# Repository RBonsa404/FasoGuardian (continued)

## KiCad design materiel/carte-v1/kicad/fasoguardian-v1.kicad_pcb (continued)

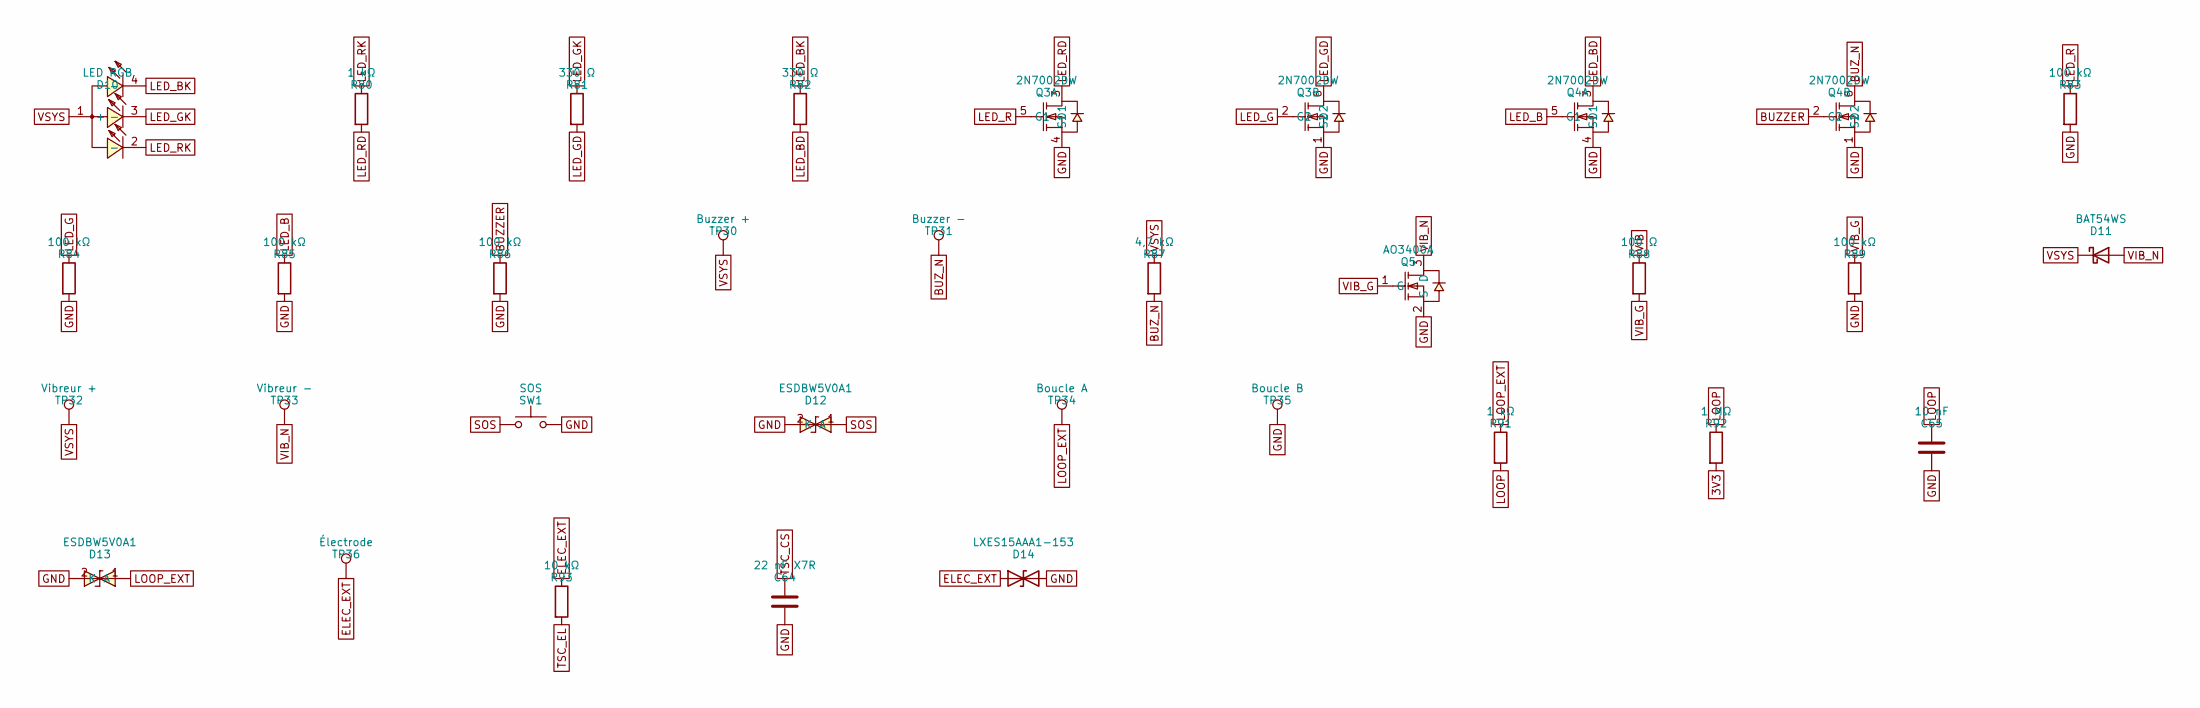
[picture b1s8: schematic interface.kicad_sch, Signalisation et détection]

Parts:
C64: 22 nF X7R; C_0402_1005Metric; LCSC C1532
C65: 10 nF; C_0402_1005Metric; LCSC C15195
D10: LED RGB; LED-ARRAY-SMD_4P-L1.0-W1.0-TR-RD; LCSC C158099
D11: BAT54WS; D_SOD-323; LCSC C22629
D12, D13: ESDBW5V0A1; X1-DFN1006-2_L1.0-W0.6-P0.65-BI; LCSC C5173252
D14: LXES15AAA1-153; D_0402_1005Metric; LCSC C5210978
Q3, Q4: 2N7002DW; SOT-363_L2.0-W1.3-P0.65-LS2.1-TL; LCSC C83571
Q5: AO3400A; SOT-23-3_L2.9-W1.3-P1.90-LS2.4-BR; LCSC C20917
R80, R91: 1 kΩ; R_0402_1005Metric; LCSC C11702
R81, R82: 330 Ω; R_0402_1005Metric; LCSC C25104
R83, R84, R85, R86, R89: 100 kΩ; R_0402_1005Metric; LCSC C25741
R87: 4,7 kΩ; R_0402_1005Metric; LCSC C25900
R88: 100 Ω; R_0402_1005Metric; LCSC C25076
R92: 1 MΩ; R_0402_1005Metric; LCSC C26083
R93: 10 kΩ; R_0402_1005Metric; LCSC C25744
SW1: SOS; SW_SPST_EVQP7A; LCSC C79167
TP30: Buzzer +; TestPoint_Pad_1.5x1.5mm
TP31: Buzzer −; TestPoint_Pad_1.5x1.5mm
TP32: Vibreur +; TestPoint_Pad_1.5x1.5mm
TP33: Vibreur −; TestPoint_Pad_1.5x1.5mm
TP34: Boucle A; TestPoint_Pad_1.5x1.5mm
TP35: Boucle B; TestPoint_Pad_1.5x1.5mm
TP36: Électrode; TestPoint_Pad_1.5x1.5mm

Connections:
3V3: R92.2; also elsewhere on the board
BUZZER: Q4.2 (G2), R86.1; also elsewhere on the board
BUZ_N: Q4.6 (D2), R87.2, TP31.1
ELEC_EXT: D14.1 (A1), R93.1, TP36.1
GND: C64.2, C65.2, D12.2 (A), D13.2 (A), D14.2 (A2), Q3.1 (S2), Q3.4 (S1), Q4.1 (S2), Q4.4 (S1), Q5.2 (S), R83.2, R84.2, R85.2, R86.2, R89.2, SW1.2, TP35.1; also elsewhere on the board
LED_B: Q4.5 (G1), R85.1; also elsewhere on the board
LED_BD: Q4.3 (D1), R82.2
LED_BK: D10.4 (-), R82.1
LED_G: Q3.2 (G2), R84.1; also elsewhere on the board
LED_GD: Q3.6 (D2), R81.2
LED_GK: D10.3 (-), R81.1
LED_R: Q3.5 (G1), R83.1; also elsewhere on the board
LED_RD: Q3.3 (D1), R80.2
LED_RK: D10.2 (-), R80.1
LOOP: C65.1, R91.2, R92.1; also elsewhere on the board
LOOP_EXT: D13.1 (K), R91.1, TP34.1
SOS: D12.1 (K), SW1.1; also elsewhere on the board
TSC_CS: C64.1; also elsewhere on the board
TSC_EL: R93.2; also elsewhere on the board
VIB: R88.1; also elsewhere on the board
VIB_G: Q5.1 (G), R88.2, R89.1
VIB_N: D11.2 (A), Q5.3 (D), TP33.1
VSYS: D10.1 (+), D11.1 (K), R87.1, TP30.1, TP32.1; also elsewhere on the board

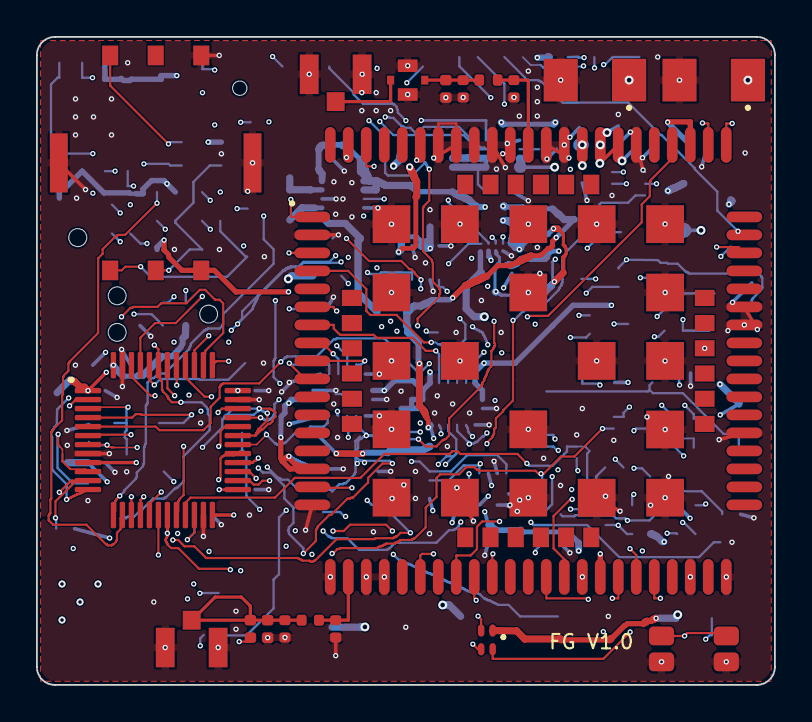
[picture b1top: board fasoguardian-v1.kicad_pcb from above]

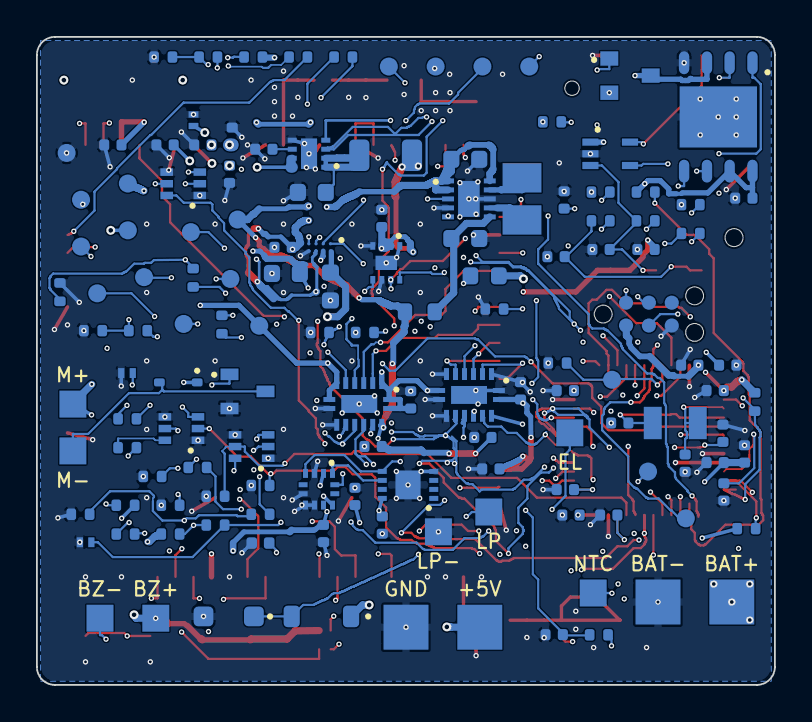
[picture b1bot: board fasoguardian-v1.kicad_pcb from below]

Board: 6 copper layers, 41.0 x 36.0 mm, 155 parts (136 on the bottom side), 107 nets.

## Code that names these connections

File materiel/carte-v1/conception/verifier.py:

"""Point de contrôle de l'étape 1 : règles de conception vérifiées sur la netlist de référence.

Usage : python verifier.py — sort en erreur si une règle n'est pas tenue.
"""
from __future__ import annotations

import re
import sys
from collections import defaultdict

import bibliotheques as bib
from carte import ADRESSES_I2C, ALIMENTATIONS, COMPOSANTS, RAILS_DECOUPLES

# Affectation des broches du STM32U585CIT6, brochage identique au STM32U575CIT6 : FG-DOC-08 tableau 8, avec les
# écarts de CAHIER.md § 5.
TABLEAU_8 = {
    'PA9': 'MCU_TX', 'PA10': 'MCU_RX', 'PA11': 'MCU_CTS', 'PA12': 'MCU_RTS',
    'PB5': 'RI_3V3', 'PB2': 'STATUS_3V3', 'PB6': 'I2C_SCL', 'PB7': 'I2C_SDA', 'PA15': 'ACC_INT1', 'PA1': 'CHG_INT',
    'PA2': 'GAUGE_ALRT', 'PA0': 'LOOP', 'PB12': 'TSC_CS', 'PB13': 'TSC_EL', 'PA8': 'SOS',
    'PA5': 'SPI_SCK', 'PA6': 'SPI_MISO', 'PA7': 'SPI_MOSI', 'PA4': 'FLASH_CS', 'PB8': 'FLASH_PWR_N',
    'PB0': 'LED_R', 'PB1': 'LED_G', 'PB10': 'LED_B', 'PB14': 'BUZZER', 'PA13': 'SWDIO', 'PA14': 'SWCLK',
    # Écarts justifiés (CAHIER.md § 5)
    'PB9': 'VIB', 'PC13': 'MCU_PWRKEY', 'PH1': 'MCU_RESET', 'PH0': 'MODEM_EN', 'PB4': 'MCU_DTR', 'PA3': 'NTC_MES',
    'PB3': 'NTC_EN', 'PB15': 'NETLIGHT_3V3',
}
# Fonctions alternatives exigées (fiche ST, symbole KiCad).
ALTERNATIVES = {
    'PA9': 'USART1_TX', 'PA10': 'USART1_RX', 'PA11': 'USART1_CTS', 'PA12': 'USART1_RTS', 'PB6': 'I2C1_SCL',
    'PB7': 'I2C1_SDA', 'PA5': 'SPI1_SCK', 'PA6': 'SPI1_MISO', 'PA7': 'SPI1_MOSI', 'PB12': 'TSC_G1_IO1',
    'PB13': 'TSC_G1_IO2', 'PB0': 'TIM3_CH3', 'PB1': 'TIM3_CH4', 'PB10': 'TIM2_CH3', 'PB14': 'TIM15_CH1',
    'PB9': 'TIM4_CH4', 'PA3': 'ADC1_IN8',
}

erreurs: list[str] = []
avertissements: list[str] = []


def erreur(message: str) -> None:
    erreurs.append(message)


par_ref = {c.ref: c for c in COMPOSANTS}
reseaux: dict[str, list[tuple[str, str]]] = defaultdict(list)

# 1. Symboles, empreintes et broches.
references = [c.ref for c in COMPOSANTS]
for ref in {r for r in references if references.count(r) > 1}:
    erreur(f'référence en double : {ref}')
for c in COMPOSANTS:
    try:
        broches = bib.broches_symbole(c.symbole)
        plots = bib.plots_empreinte(c.empreinte)
    except (KeyError, ValueError) as e:
        erreur(f'{c.ref} : {e}')
        continue
    for numero in c.broches:
        if numero not in broches:
            erreur(f'{c.ref} : broche {numero} absente du symbole {c.symbole}')
    for numero in broches:
        if numero not in c.broches and numero not in c.libres:
            erreur(f'{c.ref} : broche {numero} ({broches[numero]["nom"]}) ni reliée ni déclarée libre')
    for numero in plots:
        if numero not in broches and numero not in c.libres:
            erreur(f'{c.ref} : plot {numero} de {c.empreinte} sans broche')
    for numero in broches:
        if numero not in plots:
            erreur(f'{c.ref} : broche {numero} sans plot dans {c.empreinte}')
    for numero, reseau in c.broches.items():
        reseaux[reseau].append((c.ref, numero))

# 2. Réseaux à une seule extrémité (hors points de test volontaires).
for reseau, extremites in reseaux.items():
    if len(extremites) < 2:
        erreur(f'réseau {reseau} relié à une seule broche : {extremites}')

# 3. Tableau 8 et fonctions alternatives.
u1 = par_ref['U1']
noms_u1 = {b['nom']: n for n, b in bib.broches_symbole(u1.symbole).items()}
definition_u1 = bib.symbole(u1.symbole)
for port, reseau in TABLEAU_8.items():
    numero = noms_u1.get(port)
    if numero is None:
        erreur(f'{port} absente du boîtier LQFP48')
    elif u1.broches.get(numero) != reseau:
        erreur(f'{port} (broche {numero}) reliée à {u1.broches.get(numero)} au lieu de {reseau}')
for port, fonction in ALTERNATIVES.items():
    m = re.search(r'\(pin \w+ \w+\s*\(at [^)]*\)[^()]*(\([^()]*\)[^()]*)*?\(name "%s"' % port, definition_u1)
    debut = definition_u1.find(f'(name "{port}"')
    fin = definition_u1.find('(pin ', debut)
    if fonction not in definition_u1[debut:fin if fin > 0 else None]:
        erreur(f'{port} ne propose pas {fonction}')

# 4. Domaines de tension : aucune broche logique du module (1,8 V, 2,0 V au plus) sur un réseau du microcontrôleur.
u2 = par_ref['U2']
broches_u2 = bib.broches_symbole(u2.symbole)
for numero, reseau in u2.broches.items():
    nom = broches_u2[numero]['nom']
    if reseau in ALIMENTATIONS or nom in ('PWRKEY', 'RESET') or reseau.startswith(('RF_', 'SIM_', 'GNSS_', 'MOD_U3', 'MOD_MKIN3')):
        continue
    for ref, n in reseaux[reseau]:
        if ref == 'U1' or (par_ref[ref].symbole == 'Device:R' and '3V3' in par_ref[ref].broches.values()):
            erreur(f'U2.{numero} ({nom}, 1,8 V) relié au domaine 3,3 V par {ref}.{n}')
# PWRKEY et RESET : seulement le module et un drain de NMOS.
for reseau in ('MOD_PWRKEY', 'MOD_RESET'):
    if sorted(r for r, _ in reseaux[reseau]) != ['Q1', 'U2']:
        erreur(f'{reseau} doit relier seulement U2 et le drain de Q1 : {reseaux[reseau]}')
    for ref, _ in reseaux[reseau]:
        if par_ref[ref].symbole == 'Device:C':
            erreur(f'condensateur sur {reseau} (100 nF au plus, SIMCom § 3.2.1)')

# 5. Bus I²C : adresses distinctes, rappels présents.
if len(set(ADRESSES_I2C.values())) != len(ADRESSES_I2C):
    erreur(f'adresses I²C en conflit : {ADRESSES_I2C}')
for ligne in ('I2C_SCL', 'I2C_SDA'):
    if not any(par_ref[r].symbole == 'Device:R' and '3V3' in par_ref[r].broches.values() for r, _ in reseaux[ligne]):
        erreur(f'{ligne} sans résistance de rappel')


# 6. Capacités par rail.
def capacite(valeur: str) -> float:
    m = re.match(r'([\d,]+)\s*(pF|nF|µF)', valeur)
    if not m:
        return 0.0
    return float(m.group(1).replace(',', '.')) * {'pF': 1e-12, 'nF': 1e-9, 'µF': 1e-6}[m.group(2)]


def total(reseau: str) -> float:
    return sum(capacite(par_ref[r].valeur) for r, _ in reseaux[reseau]
               if par_ref[r].symbole in ('Device:C',) or 'T520' in par_ref[r].symbole if not par_ref[r].non_monte)


if total('VBAT_MODEM') < 300e-6:
    erreur(f'réservoir du modem {total("VBAT_MODEM") * 1e6:.0f} µF < 300 µF (SIMCom § 3.1.1)')
if total('VSYS') > 100e-6:
    erreur(f'capacité sur SYS {total("VSYS") * 1e6:.0f} µF > 100 µF (BQ25180)')
for valeur in ('33 pF', '10 pF', '100 nF', '1 µF'):
    if not any(par_ref[r].valeur == valeur for r, _ in reseaux['VBAT_MODEM']):
        erreur(f'découplage {valeur} absent au pied des plots VBAT du modem')
# Chaque circuit intégré a au moins un condensateur sur chacun de ses rails.
for c in COMPOSANTS:
    if not c.ref.startswith('U'):
        continue
    for reseau in {r for r in c.broches.values() if r in RAILS_DECOUPLES and r != 'GND'}:
        if not any(par_ref[r].symbole == 'Device:C' or 'T520' in par_ref[r].symbole for r, _ in reseaux[reseau]):
            erreur(f'{c.ref} : aucun condensateur sur {reseau}')

# 7. Faces : les pièces hautes sur la face supérieure ; la hauteur de chaque pièce de la face inférieure (1,35 mm au
# plus, d'après les fiches) est contrôlée sur la carte placée par modeles_3d.py.
HAUTES = ('fg:A7670E', 'fg:T520', 'fg:NANOSIM', 'fg:U.FL', 'fg:SM03B', 'fg:ECT8', 'Switch:', 'MCU_ST', 'fg:FC-B1010')
for c in COMPOSANTS:
    if c.face == 'B' and c.symbole.startswith(HAUTES):
        erreur(f'{c.ref} ({c.symbole}) trop haut pour la face inférieure')

print(f'{len(COMPOSANTS)} composants, {len(reseaux)} réseaux, {sum(len(v) for v in reseaux.values())} broches reliées')
print(f'réservoir modem {total("VBAT_MODEM") * 1e6:.0f} µF, capacité SYS {total("VSYS") * 1e6:.1f} µF')
for message in avertissements:
    print('AVERTISSEMENT', message)
for message in erreurs:
    print('ERREUR', message)
sys.exit(1 if erreurs else 0)
